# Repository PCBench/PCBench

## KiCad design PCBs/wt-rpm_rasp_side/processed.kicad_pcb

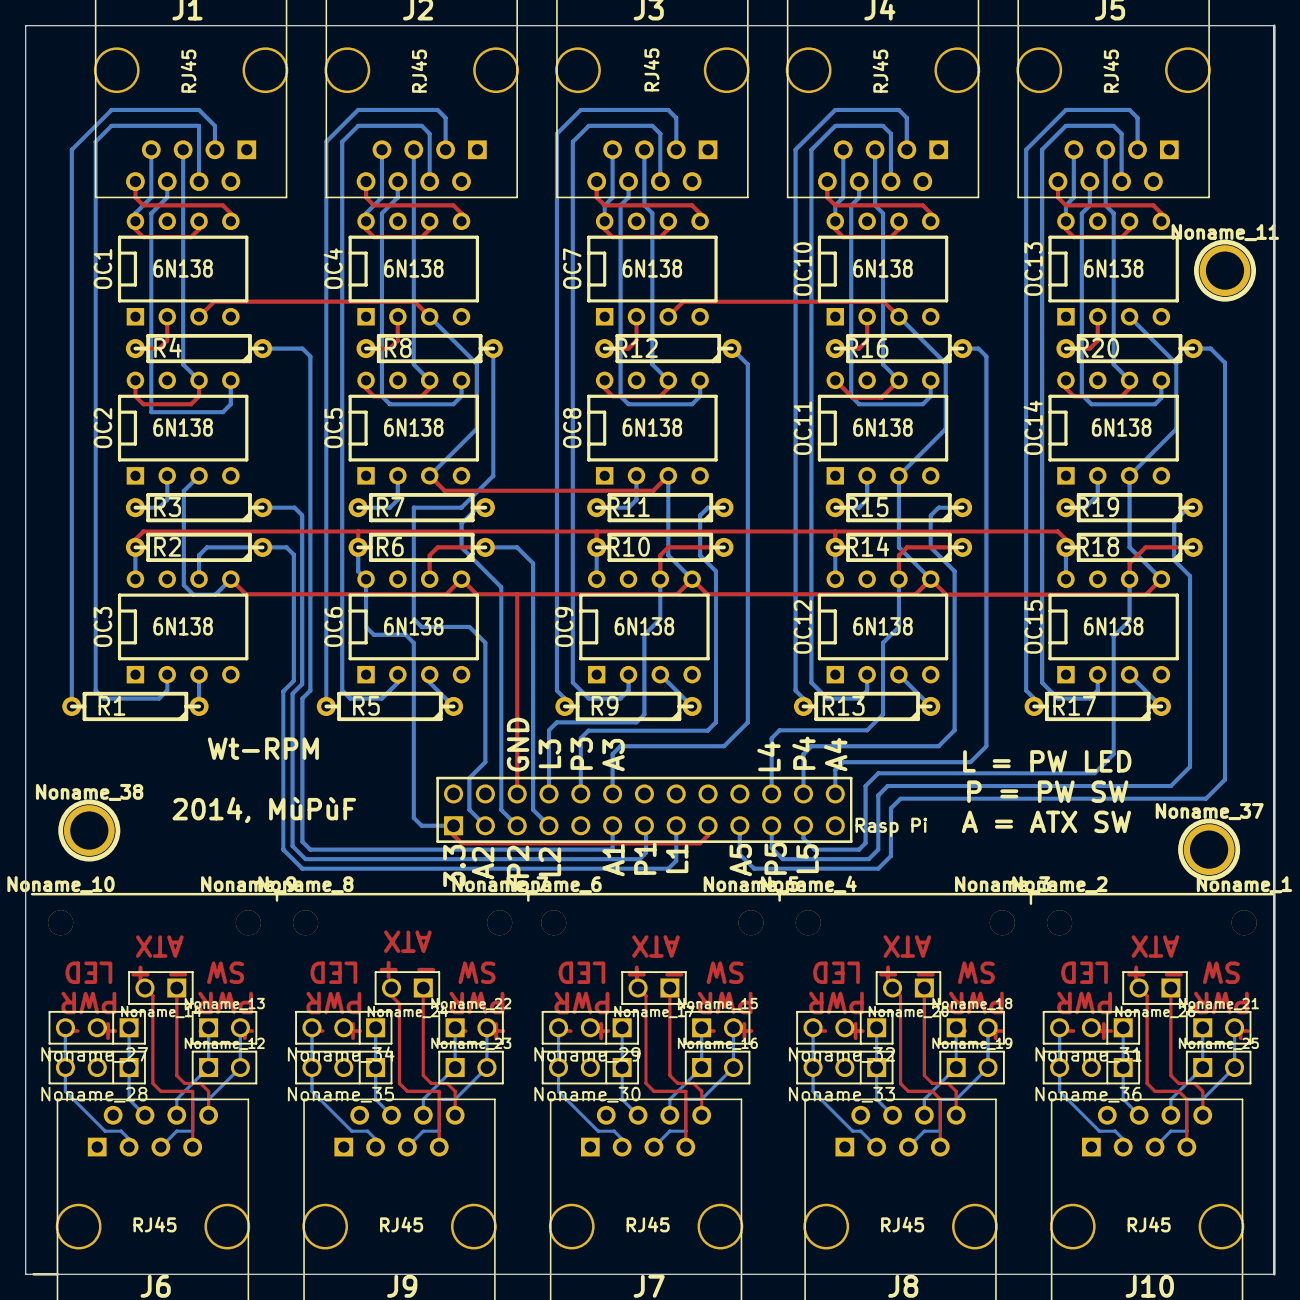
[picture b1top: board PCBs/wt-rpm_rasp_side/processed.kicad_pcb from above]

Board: 2 copper layers, 99.7 x 99.7 mm, 84 parts (0 on the bottom side), 92 nets.

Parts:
J1, J2, J3, J4, J5, J6, J7, J8, J9, J10: RJ45; RJ45_8
Noname_1, Noname_2, Noname_3, Noname_4, Noname_5, Noname_6, Noname_7, Noname_8, Noname_9, Noname_10: small_hole
Noname_11, Noname_37, Noname_38: 1pin
Noname_12, Noname_13, Noname_14, Noname_15, Noname_16, Noname_17, Noname_18, Noname_19, Noname_20, Noname_21, Noname_22, Noname_23, Noname_24, Noname_25, Noname_26: PIN_ARRAY_2X1
Noname_27, Noname_28, Noname_29, Noname_30, Noname_31, Noname_32, Noname_33, Noname_34, Noname_35, Noname_36: PIN_ARRAY_3X1
OC1, OC2, OC3, OC4, OC5, OC6, OC7, OC8, OC9, OC10, OC11, OC12, OC13, OC14, OC15: 6N138; DIP-8__300
R1, R5, R9, R13, R17: 4k; R4
R2, R6, R10, R14, R18: 10k; R4
R3, R4, R7, R8, R11, R12, R15, R16, R19, R20: 1.2k; R4
Rasp Pi: pin_array_13x2

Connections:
+3.3V: OC3.8, OC6.8, OC9.8, OC12.8, OC15.8, R2.2, R6.2, R10.2, R14.2, R18.2, Rasp Pi.1, Rasp Pi.17
GND: OC1.3, OC2.3, OC3.5, OC4.3, OC5.3, OC6.5, OC7.3, OC8.3, OC9.5, OC10.3, OC11.3, OC12.5, OC13.3, OC14.3, OC15.5, Rasp Pi.6
unnamed: J5.3, R17.2
unnamed: J5.7, OC13.6, OC13.8
unnamed: J5.6, OC14.5
unnamed: J5.5, OC14.6, OC14.8
unnamed: J5.4, OC15.2
unnamed: OC15.3, R17.1
unnamed: OC14.2, R19.2
unnamed: J5.8, OC13.5
unnamed: J6.7, Noname_14.2
unnamed: J6.8, Noname_14.1
unnamed: J6.4, Noname_27.1, Noname_28.1
unnamed: J6.3, Noname_27.3, Noname_28.3
unnamed: J6.6, Noname_12.1, Noname_13.1
unnamed: OC15.6, R18.1, Rasp Pi.23
unnamed: OC13.2, R20.2
unnamed: R20.1, Rasp Pi.19
unnamed: R19.1, Rasp Pi.21
unnamed: J6.5, Noname_12.2, Noname_13.2
unnamed: OC12.6, R14.1, Rasp Pi.22
unnamed: OC10.2, R16.2
unnamed: OC11.2, R15.2
unnamed: R16.1, Rasp Pi.26
unnamed: R15.1, Rasp Pi.24
unnamed: J4.7, OC10.6, OC10.8
unnamed: J4.6, OC11.5
unnamed: J4.5, OC11.6, OC11.8
unnamed: J4.3, R13.2
unnamed: J4.4, OC12.2
unnamed: OC12.3, R13.1
unnamed: J3.7, OC7.6, OC7.8
unnamed: R3.1, Rasp Pi.13
unnamed: J9.8, Noname_24.1
unnamed: J9.7, Noname_24.2
unnamed: J9.5, Noname_22.2, Noname_23.2
unnamed: J9.4, Noname_34.1, Noname_35.1
unnamed: J9.3, Noname_34.3, Noname_35.3
unnamed: J9.6, Noname_22.1, Noname_23.1
unnamed: J10.8, Noname_26.1
unnamed: J10.7, Noname_26.2
unnamed: J10.4, Noname_31.1, Noname_36.1
unnamed: J10.3, Noname_31.3, Noname_36.3
unnamed: J10.6, Noname_21.1, Noname_25.1
unnamed: J10.5, Noname_21.2, Noname_25.2
unnamed: J7.3, Noname_29.3, Noname_30.3
unnamed: J7.6, Noname_15.1, Noname_16.1
unnamed: J7.5, Noname_15.2, Noname_16.2
unnamed: J7.8, Noname_17.1
unnamed: J7.4, Noname_29.1, Noname_30.1
unnamed: J7.7, Noname_17.2
unnamed: J8.7, Noname_20.2
unnamed: J8.8, Noname_20.1
unnamed: J8.6, Noname_18.1, Noname_19.1
unnamed: J8.5, Noname_18.2, Noname_19.2
unnamed: J8.4, Noname_32.1, Noname_33.1
unnamed: J8.3, Noname_32.3, Noname_33.3
unnamed: OC3.3, R1.1
unnamed: J1.6, OC2.5
unnamed: J1.5, OC2.6, OC2.8
unnamed: J1.4, OC3.2
unnamed: J1.3, R1.2
unnamed: OC3.6, R2.1, Rasp Pi.15
unnamed: J1.7, OC1.6, OC1.8
unnamed: J1.8, OC1.5
unnamed: OC6.6, R6.1, Rasp Pi.7
unnamed: OC6.3, R5.1
unnamed: J2.3, R5.2
unnamed: R8.1, Rasp Pi.3
unnamed: OC4.2, R8.2
unnamed: R7.1, Rasp Pi.5
unnamed: OC1.2, R4.2
unnamed: OC2.2, R3.2
unnamed: R4.1, Rasp Pi.11
unnamed: OC5.2, R7.2
unnamed: J2.6, OC5.5
unnamed: J2.5, OC5.6, OC5.8
unnamed: J2.4, OC6.2
unnamed: J2.8, OC4.5
unnamed: J3.3, R9.2
unnamed: J3.8, OC7.5
unnamed: J4.8, OC10.5
unnamed: OC9.3, R9.1
unnamed: OC9.6, R10.1, Rasp Pi.8
unnamed: OC7.2, R12.2
unnamed: OC8.2, R11.2
unnamed: R12.1, Rasp Pi.12
unnamed: R11.1, Rasp Pi.10
unnamed: J3.5, OC8.6, OC8.8
unnamed: J3.6, OC8.5
unnamed: J3.4, OC9.2
unnamed: J2.7, OC4.6, OC4.8

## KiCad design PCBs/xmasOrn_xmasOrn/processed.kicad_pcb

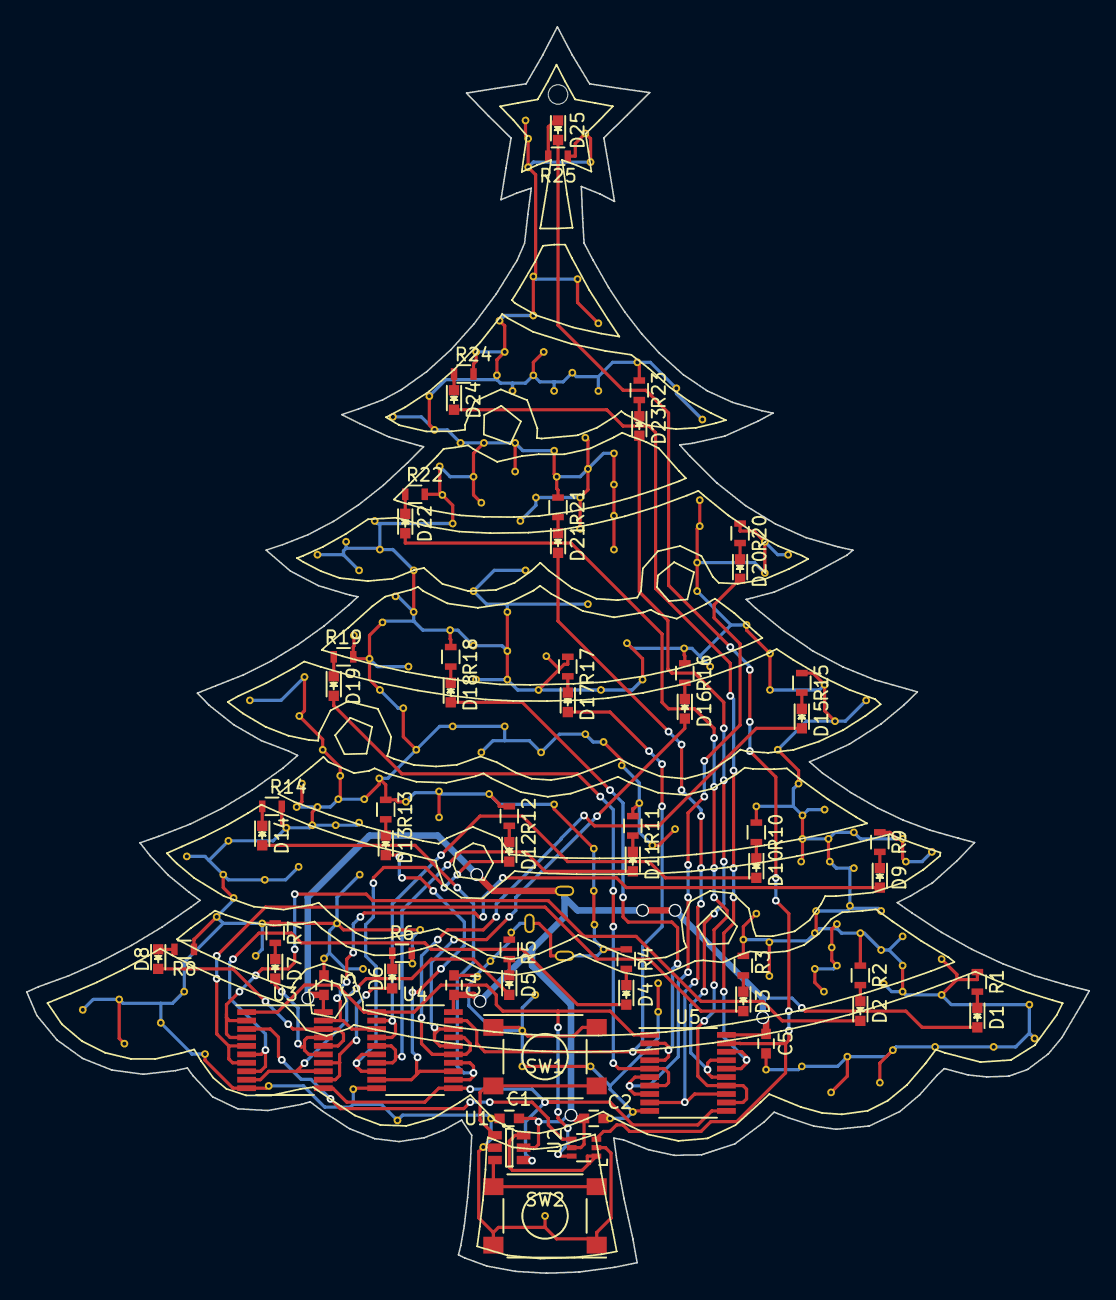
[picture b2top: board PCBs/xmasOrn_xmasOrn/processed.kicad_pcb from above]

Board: 2 copper layers, 81.7 x 95.9 mm, 64 parts (1 on the bottom side), 57 nets.

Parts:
C1: 0.1u; C_0603
C2, C3, C4, C5: 10u; C_0603
CON1: BARREL_JACK; PJ-007
D1, D2, D3, D4, D5, D6, D7, D8, D9, D10, D11, D12, D13, D14, D15, D16, D17, D18, D19, D20, D21, D22, D23, D24, D25: LED; LED_0603
R1, R2, R3, R4, R5, R6, R7, R8, R9, R10, R11, R12, R13, R14, R15, R16, R17, R18, R19, R20, R21, R22, R23, R24, R25: 560; R_0603
SW1, SW2: SW_PUSH; ADTSM6
U1: MAX6817; SOT-23-6
U2: NC7WZ14; SC-70-6
U3, U4, U5: SN74ABT273; TSSOP-20_4.4x6.5mm_Pitch0.65mm
svg2mod: G***; xmastreeSS

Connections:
/CLK: U1.4, U3.11, U4.11, U5.11
/CLKIN: SW2.2, U1.3
/CLR: U1.6, U2.1
/CLRBAR: U2.6, U3.1, U4.1, U5.1
/CLRIN: SW1.2, U1.1
/O2: D2.2, U3.2, U3.4
/O3: D3.2, U3.5, U3.7
/O4: D4.2, U3.6, U3.8
/O5: D5.2, U3.9, U3.13
/O6: D6.2, U3.12, U3.14
/O7: D7.2, U3.15, U3.17
/O8: D8.2, U3.16, U3.18
/O9: D9.2, U3.19, U4.3
/O10: D10.2, U4.2, U4.4
/O11: D11.2, U4.5, U4.7
/O12: D12.2, U4.6, U4.8
/O13: D13.2, U4.9, U4.13
/O14: D14.2, U4.12, U4.14
/O15: D15.2, U4.15, U4.17
/O16: D16.2, U4.16, U4.18
/O17: D17.2, U4.19, U5.3
/O18: D18.2, U5.2, U5.4
/O19: D19.2, U5.5, U5.7
/O20: D20.2, U5.6, U5.8
/O21: D21.2, U5.9, U5.13
/O22: D22.2, U5.12, U5.14
/O23: D23.2, U5.15, U5.17
/O24: D24.2, U5.16, U5.18
/O25: D25.2, U2.3, U5.19
/O25B: U2.4, U3.3
GND: C1.1, C2.1, C3.1, C4.1, C5.1, CON1.2, CON1.3, R1.1, R2.1, R3.1, R4.1, R5.1, R6.1, R7.1, R8.1, R9.1, R10.1, R11.1, R12.1, R13.1, R14.1, R15.1, R16.1, R17.1, R18.1, R19.1, R20.1, R21.1, R22.1, R23.1, R24.1, R25.1, SW1.1, SW2.1, U1.2, U2.2, U3.10, U4.10, U5.10
unnamed: D1.1, R1.2
unnamed: D2.1, R2.2
unnamed: D3.1, R3.2
unnamed: D4.1, R4.2
unnamed: D5.1, R5.2
unnamed: D6.1, R6.2
unnamed: D7.1, R7.2
unnamed: D8.1, R8.2
unnamed: D9.1, R9.2
unnamed: D10.1, R10.2
unnamed: D11.1, R11.2
unnamed: D12.1, R12.2
unnamed: D13.1, R13.2
unnamed: D14.1, R14.2
unnamed: D15.1, R15.2
unnamed: D16.1, R16.2
unnamed: D17.1, R17.2
unnamed: D18.1, R18.2
unnamed: D19.1, R19.2
unnamed: D20.1, R20.2
unnamed: D21.1, R21.2
unnamed: D22.1, R22.2
unnamed: D23.1, R23.2
unnamed: D24.1, R24.2
unnamed: D25.1, R25.2
VCC: C1.2, C2.2, C3.2, C4.2, C5.2, CON1.1, D1.2, U1.5, U2.5, U3.20, U4.20, U5.20

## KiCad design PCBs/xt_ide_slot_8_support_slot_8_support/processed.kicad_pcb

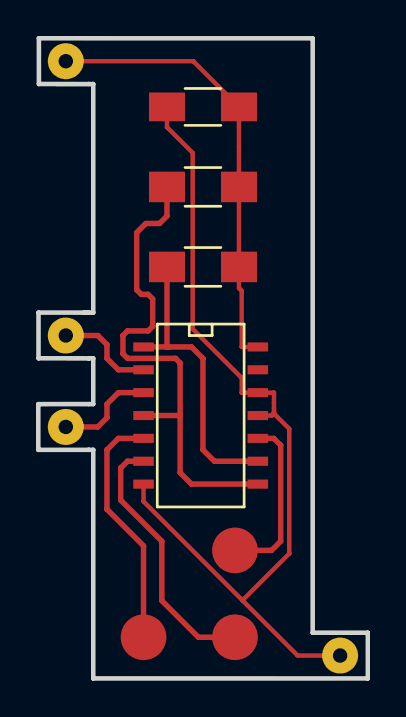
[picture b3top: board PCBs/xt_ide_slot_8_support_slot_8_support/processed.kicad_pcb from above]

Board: 2 copper layers, 18.3 x 35.6 mm, 11 parts (0 on the bottom side), 9 nets.

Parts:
/CS_ROM1: CONN_1; SolderWirePad_single_0-8mmDrill
/MEMR1: CONN_1; SolderWirePad_single_0-8mmDrill
C1: 0.1uF; C_1206_HandSoldering
P6, P7: CONN_1; SolderWirePad_single_0-8mmDrill
R1, R2: 10K; R_1206_HandSoldering
TP1, TP2, TP3: CONN_1; SMD_TESTPOINT
U1: 74LS33; SOIC-14_N

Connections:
GND: C1.2, P7.1, U1.7, U1.11, U1.12
unnamed: /CS_ROM1.1, U1.3
unnamed: /MEMR1.1, U1.2
unnamed: R1.2, U1.4, U1.8
unnamed: R2.2, U1.1, U1.9
unnamed: TP1.1, U1.10
unnamed: TP2.1, U1.5
unnamed: TP3.1, U1.6
VCC: C1.1, P6.1, R1.1, R2.1, U1.14

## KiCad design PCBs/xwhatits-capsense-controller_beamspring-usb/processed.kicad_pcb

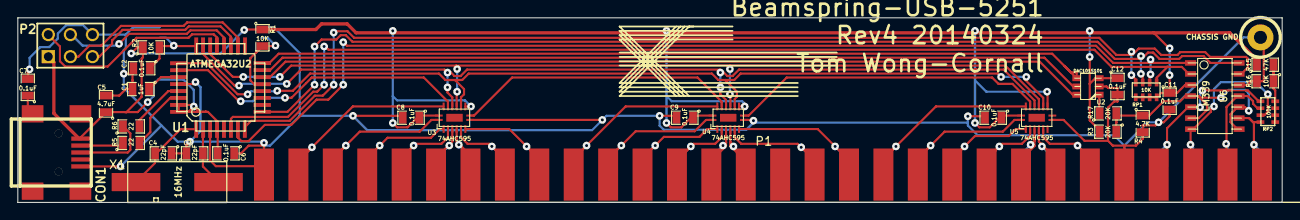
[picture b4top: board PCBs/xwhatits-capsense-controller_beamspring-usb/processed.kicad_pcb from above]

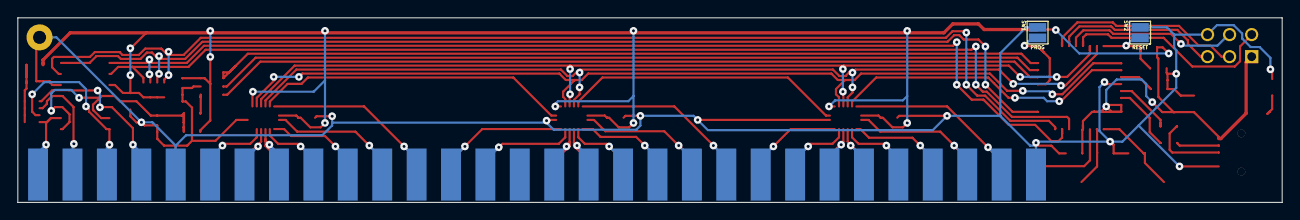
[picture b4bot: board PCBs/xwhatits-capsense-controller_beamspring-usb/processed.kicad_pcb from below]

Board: 2 copper layers, 145.5 x 21.2 mm, 36 parts (2 on the bottom side), 59 nets.

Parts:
C1: 1uF; SM0805
C2, C6, C7, C8, C9, C10, C11, C12: 0.1uF; SM0805
C3, C4: 22pF; SM0805
C5: 4.7uF; SM0805
CHASSIS GND: P***; 1pin
CON1: USB-MINI-B; USB_MINI_B
P1: EDGE_30X2; 805_396_30x2_SM
P2: CONN_3X2; pin_array_3x2
R1, R2, R16: 10K; SM0805
R3, R17: 20K; SM0805
R4: 4.7K; SM0805
R5, R6: 22; SM0805
R15: 47K; SM0805
RP1: 10K; RPACK_1206
RP2: 100K; RPACK_1206
SW1: PROG; TEST_BRIDGE_SM
SW2: RESET; TEST_BRIDGE_SM
U1: ATMEGA32U2; TQFP32
U2: DAC101S101; tsot-6
U3, U4, U5: 74AHC595; DHVQFN16
U6: LM339; so-14
X1: 16MHz; HC49US

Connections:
/SR_DS: U1.26, U3.14
/SR_OE: U1.23, U3.13, U4.13, U5.13
/SR_SHCP: U1.25, U3.11, U4.11, U5.11
/SR_STCP: U1.22, U3.12, U4.12, U5.12
GND: C1.2, C2.2, C3.1, C4.1, C5.2, C6.1, C7.2, C8.2, C9.2, C10.2, C11.2, C12.2, CHASSIS GND.1, CON1.5, P1.1, P1.26, P1.31, P1.56, P2.6, R4.2, R16.2, SW1.1, SW2.2, U1.3, U1.28, U2.2, U3.8, U4.8, U5.8, U6.12
unnamed: R15.2, R16.1, RP2.1, RP2.2, RP2.3, RP2.4
unnamed: U1.16, U2.4
unnamed: U1.14, U2.6
unnamed: U1.15, U2.5
unnamed: R17.1, U2.1
unnamed: U4.9, U5.14
unnamed: C4.2, U1.1, X1.2
unnamed: CON1.2, R5.1
unnamed: C7.1, CON1.7
unnamed: R5.2, U1.30
unnamed: R6.2, U1.29
unnamed: CON1.3, R6.1
unnamed: C2.1, R2.2, SW2.1, U1.24
unnamed: C1.1, U1.27
unnamed: R1.2, SW1.2, U1.13
unnamed: R3.1, R4.1, R17.2, U6.4, U6.6, U6.8, U6.10
unnamed: RP1.1, U1.6, U6.2
unnamed: RP1.2, U1.7, U6.1
unnamed: P2.2, U1.21
unnamed: RP1.3, U1.9, U6.14
unnamed: RP1.4, U1.8, U6.13
unnamed: P2.3, U1.18
unnamed: P2.5, U1.19
unnamed: P2.4, U1.20
unnamed: U3.9, U4.14
unnamed: P1.7, P1.37, U3.5
unnamed: P1.2, P1.32, U3.15
unnamed: P1.3, P1.33, U3.1
unnamed: P1.4, P1.34, U3.2
unnamed: P1.5, P1.35, U3.3
unnamed: P1.6, P1.36, U3.4
unnamed: P1.8, P1.38, U3.6
unnamed: P1.9, P1.39, U3.7
unnamed: P1.10, P1.40, U4.15
unnamed: P1.20, P1.50, U5.1
unnamed: P1.30, P1.60, RP2.8, U6.9
unnamed: P1.11, P1.41, U4.1
unnamed: P1.21, P1.51, U5.2
unnamed: P1.18, P1.48, U4.7
unnamed: P1.17, P1.47, U4.6
unnamed: P1.27, P1.57, RP2.5, U6.5
unnamed: P1.28, P1.58, RP2.7, U6.7
unnamed: P1.19, P1.49, U5.15
unnamed: P1.29, P1.59, RP2.6, U6.11
unnamed: P1.12, P1.42, U4.2
unnamed: P1.22, P1.52, U5.3
unnamed: P1.13, P1.43, U4.3
unnamed: P1.23, P1.53, U5.4
unnamed: P1.14, P1.44, U4.4
unnamed: P1.24, P1.54, U5.5
unnamed: P1.15, P1.45, U4.5
unnamed: P1.25, P1.55, U5.6
unnamed: C3.2, U1.2, X1.1
VCC: C5.1, C6.2, C8.1, C9.1, C10.1, C11.1, C12.1, CON1.1, P2.1, R1.1, R2.1, R3.2, R15.1, RP1.5, RP1.6, RP1.7, RP1.8, U1.4, U1.31, U1.32, U2.3, U3.10, U3.16, U4.10, U4.16, U5.10, U5.16, U6.3

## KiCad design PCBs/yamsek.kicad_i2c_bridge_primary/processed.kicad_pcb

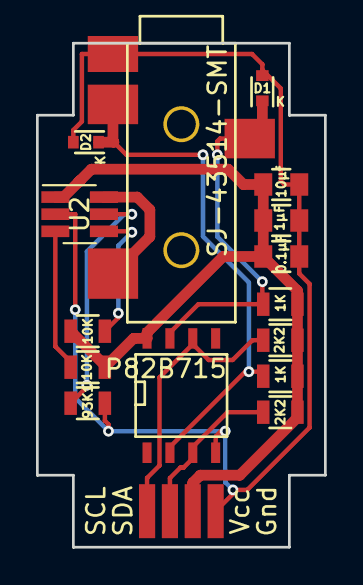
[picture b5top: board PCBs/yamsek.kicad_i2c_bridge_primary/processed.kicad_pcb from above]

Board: 2 copper layers, 16.0 x 28.0 mm, 16 parts (0 on the bottom side), 10 nets.

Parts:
C1: 10µf; C_0805
C2: 1µF; C_0805
C3: 0.1µF; C_0805
D1, D2: VESD05a1; SOD-523
I2C1: CONN_01X04; solderPads_4_Grove_I2C
R1, R2: 1K; R_0805
R3, R4: 2K2; R_0805
R5, R6: 10K; R_0805
R7: 93K1; R_0805
TRRS1: SJ-43514-SMT; audio_smd_SJ-43514-SMT
U1: P82B715; SOIC-8-N
U2: AP2553W6; SOT-23-6_Handsoldering

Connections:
+5V: C1.1, C2.1, C3.1, I2C1.3, R1.2, R2.2, R3.2, R4.2, R5.1, R6.1, U1.8, U2.1
/i2c_bridge_common/SCL_connector: D1.1, R1.1, TRRS1.3, U1.7
/i2c_bridge_common/SCL_inside: I2C1.1, R3.1, U1.6
/i2c_bridge_common/SDA_connector: D2.1, R2.1, TRRS1.4, U1.2
/i2c_bridge_common/SDA_inside: I2C1.2, R4.1, U1.3
GND: C1.2, C2.2, C3.2, D1.2, D2.2, I2C1.4, R7.2, TRRS1.1, U1.4, U2.2
unnamed: R5.2, U2.4
unnamed: R6.2, U2.3
unnamed: R7.1, U2.5
unnamed: TRRS1.2, U2.6

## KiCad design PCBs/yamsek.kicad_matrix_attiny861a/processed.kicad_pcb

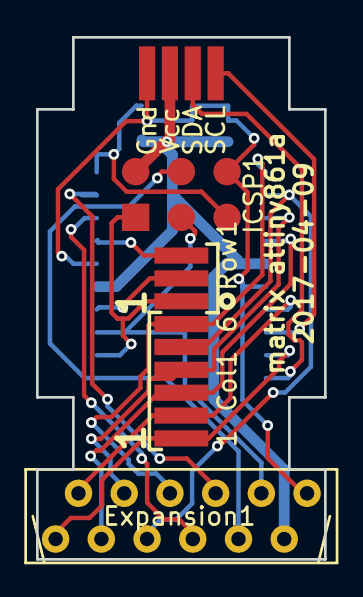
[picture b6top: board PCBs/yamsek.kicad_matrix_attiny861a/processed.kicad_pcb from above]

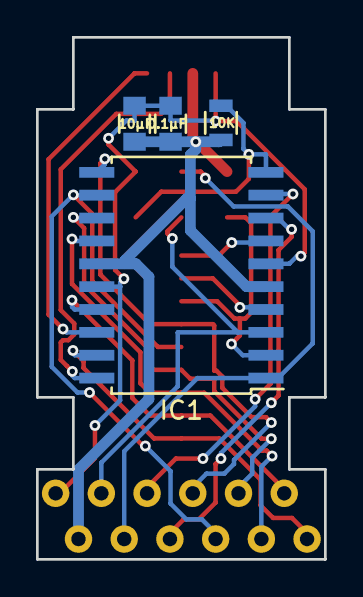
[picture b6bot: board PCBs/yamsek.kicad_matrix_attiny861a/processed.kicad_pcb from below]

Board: 2 copper layers, 16.0 x 29.0 mm, 9 parts (4 on the bottom side), 18 nets.

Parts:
C1: 10µF; C_0805
C2: 0.1µF; C_0805
Col1: CONN_01X06; solderPads_6
Expansion1: CONN_01X12; microMatch-12_90_THT
I2C1: CONN_01X04; solderPads_4_Grove_I2C
IC1: ATTINY861A-S; SOIC-20W_7.5x12.8mm_Pitch1.27mm
ICSP1: CONN_02X03; ICSP_BIG_pads
R1: 10K; R_0805
Row1: CONN_01X03; solderPads_3

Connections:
+5V: C1.1, C2.1, Expansion1.11, I2C1.3, IC1.5, IC1.15, ICSP1.2, R1.2
/ADC_H+int0: Expansion1.8, IC1.9
/ADC_V: Expansion1.7, IC1.8
/MiSo: IC1.2, ICSP1.1, Row1.1
/MoSi: Expansion1.9, IC1.1, ICSP1.4
/Rst: IC1.10, ICSP1.5, R1.1
/SCL: I2C1.1, IC1.18
/SCL_2: Expansion1.10, IC1.3, ICSP1.3
/SDA: I2C1.2, IC1.20
GND: C1.2, C2.2, Expansion1.12, I2C1.4, IC1.6, IC1.16, ICSP1.6
unnamed: Col1.1, Expansion1.1, IC1.19
unnamed: Col1.2, Expansion1.2, IC1.17
unnamed: Col1.3, Expansion1.3, IC1.14
unnamed: Col1.4, Expansion1.4, IC1.13
unnamed: Col1.5, Expansion1.5, IC1.12
unnamed: Col1.6, Expansion1.6, IC1.11
unnamed: IC1.4, Row1.2
unnamed: IC1.7, Row1.3

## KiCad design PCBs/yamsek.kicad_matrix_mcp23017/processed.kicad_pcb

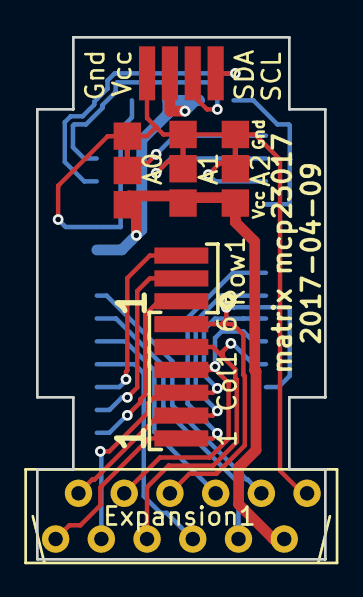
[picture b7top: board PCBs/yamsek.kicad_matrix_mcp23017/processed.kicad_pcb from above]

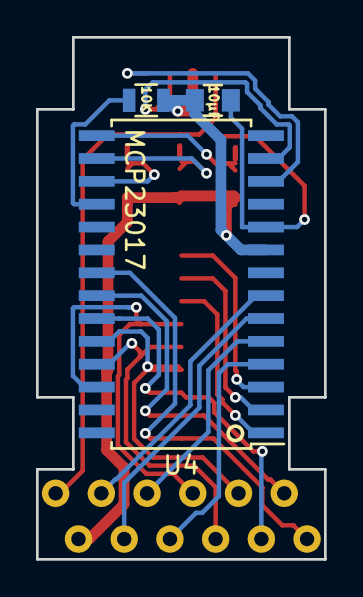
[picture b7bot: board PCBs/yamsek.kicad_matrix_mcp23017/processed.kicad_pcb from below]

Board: 2 copper layers, 16.0 x 29.0 mm, 10 parts (3 on the bottom side), 21 nets.

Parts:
A0, A1, A2: address_sel; addr_jumper
C1: 10µF; C_0805
Col1: CONN_01X06; solderPads_6
Expansion1: CONN_01X12; microMatch-12_90_THT
I2C1: CONN_01X04; solderPads_4_Grove_I2C
R1: 10K; R_0805
Row1: CONN_01X03; solderPads_3
U4: MCP23017; SOIC-28W_7.5x17.9mm_Pitch1.27mm

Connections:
+5V: A0.1, A1.1, A2.1, C1.1, Expansion1.11, I2C1.3, R1.2, U4.9
/SCL: I2C1.1, U4.12
/SDA: I2C1.2, U4.13
GND: A0.3, A1.3, A2.3, C1.2, Expansion1.12, I2C1.4, U4.10
unnamed: A0.2, U4.15
unnamed: A1.2, U4.16
unnamed: A2.2, U4.17
unnamed: Col1.1, Expansion1.1, U4.21
unnamed: Col1.2, Expansion1.2, U4.22
unnamed: Col1.3, Expansion1.3, U4.23
unnamed: Col1.4, Expansion1.4, U4.24
unnamed: Col1.5, Expansion1.5, U4.25
unnamed: Col1.6, Expansion1.6, U4.26
unnamed: Expansion1.7, U4.4
unnamed: Expansion1.8, U4.5
unnamed: Expansion1.9, U4.6
unnamed: Expansion1.10, U4.7
unnamed: R1.1, U4.18
unnamed: Row1.1, U4.1
unnamed: Row1.2, U4.2
unnamed: Row1.3, U4.3
